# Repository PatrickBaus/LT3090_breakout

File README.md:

LT3090 Breakout Board
===================

This repository contains the KiCAD PCB project files for a breakout board for the Linear Technologies LT3090 –36V, 600mA negative LDO regulator (http://www.linear.com/product/LT3090, http://www.linear.com/product/LT3090).

About
-----
This breakout board supports the LT3090 LDO regulator. The package is designed as a drop-in replacement for the popular 79xx series.

The root folder contains the KiCAD files and the bill of materials, while the gerber files can be found in the [/gerber](gerber/) folder.

Related Repositories
-------------

See the following repositories for more information

KiCAD footprints: https://github.com/PatrickBaus/footprints.pretty

KiCAD 3D models: https://github.com/PatrickBaus/footprints.3dshapes

KiCAD schematic libraries: https://github.com/PatrickBaus/KiCad-libraries

License
-------

This work is released under the Cern OHL v.1.2
See www.ohwr.org/licenses/cern-ohl/v1.2 or the included LICENSE file for more information.

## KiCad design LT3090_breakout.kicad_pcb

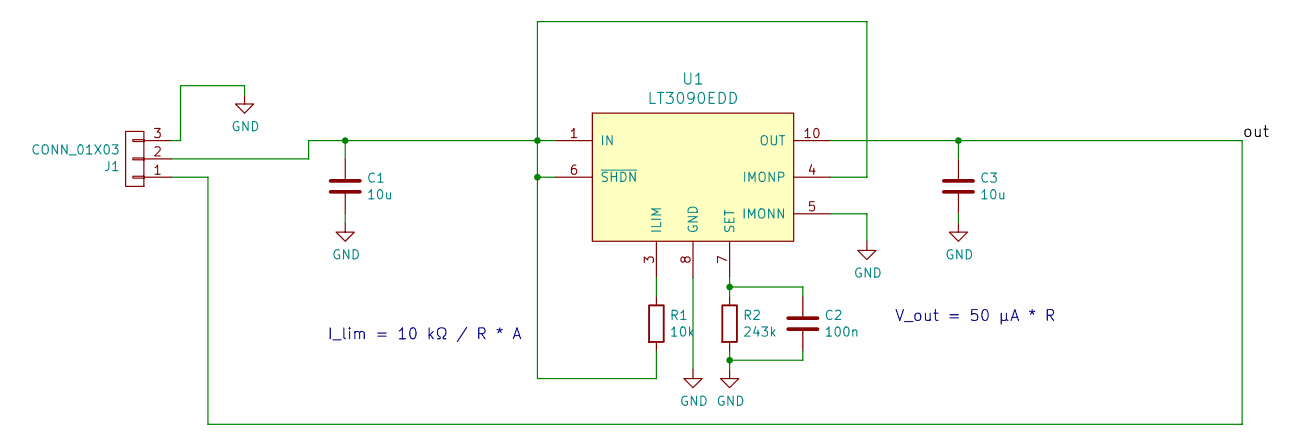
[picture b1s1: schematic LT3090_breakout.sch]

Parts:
C1, C3: 10u; C_0603
C2: 100n; C_0603
J1: CONN_01X03; Pin_Header_Angled_1x03_Pitch2.54mm
R1: 10k; R_0603
R2: 243k; R_0603
U1: LT3090EDD; DFN-10-1EP_3x3mm_Pitch0.5mm

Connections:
/out: C3.1, J1.1, U1.9 (OUT2), U1.10 (OUT)
GND: C1.2, C2.2, C3.2, J1.3, R2.2, U1.5 (IMONN), U1.8 (GND)
IN: C1.1, J1.2, R1.2, U1.1 (IN), U1.2 (IN), U1.4 (IMONP), U1.6 (~SHDN), U1.11 (PAD)
unnamed: C2.1, R2.1, U1.7 (SET)
unnamed: R1.1, U1.3 (ILIM)

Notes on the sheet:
I_lim = 10 kΩ / R * A
V_out = 50 µA * R

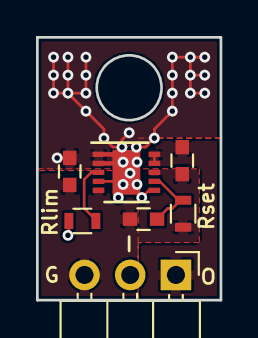
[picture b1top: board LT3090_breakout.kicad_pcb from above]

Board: 2 copper layers, 10.2 x 14.6 mm, 7 parts (0 on the bottom side), 5 nets.

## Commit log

2017-08-12 Added dependencies
2017-08-16 Added readme
2017-08-26 Added zipped gerber files
